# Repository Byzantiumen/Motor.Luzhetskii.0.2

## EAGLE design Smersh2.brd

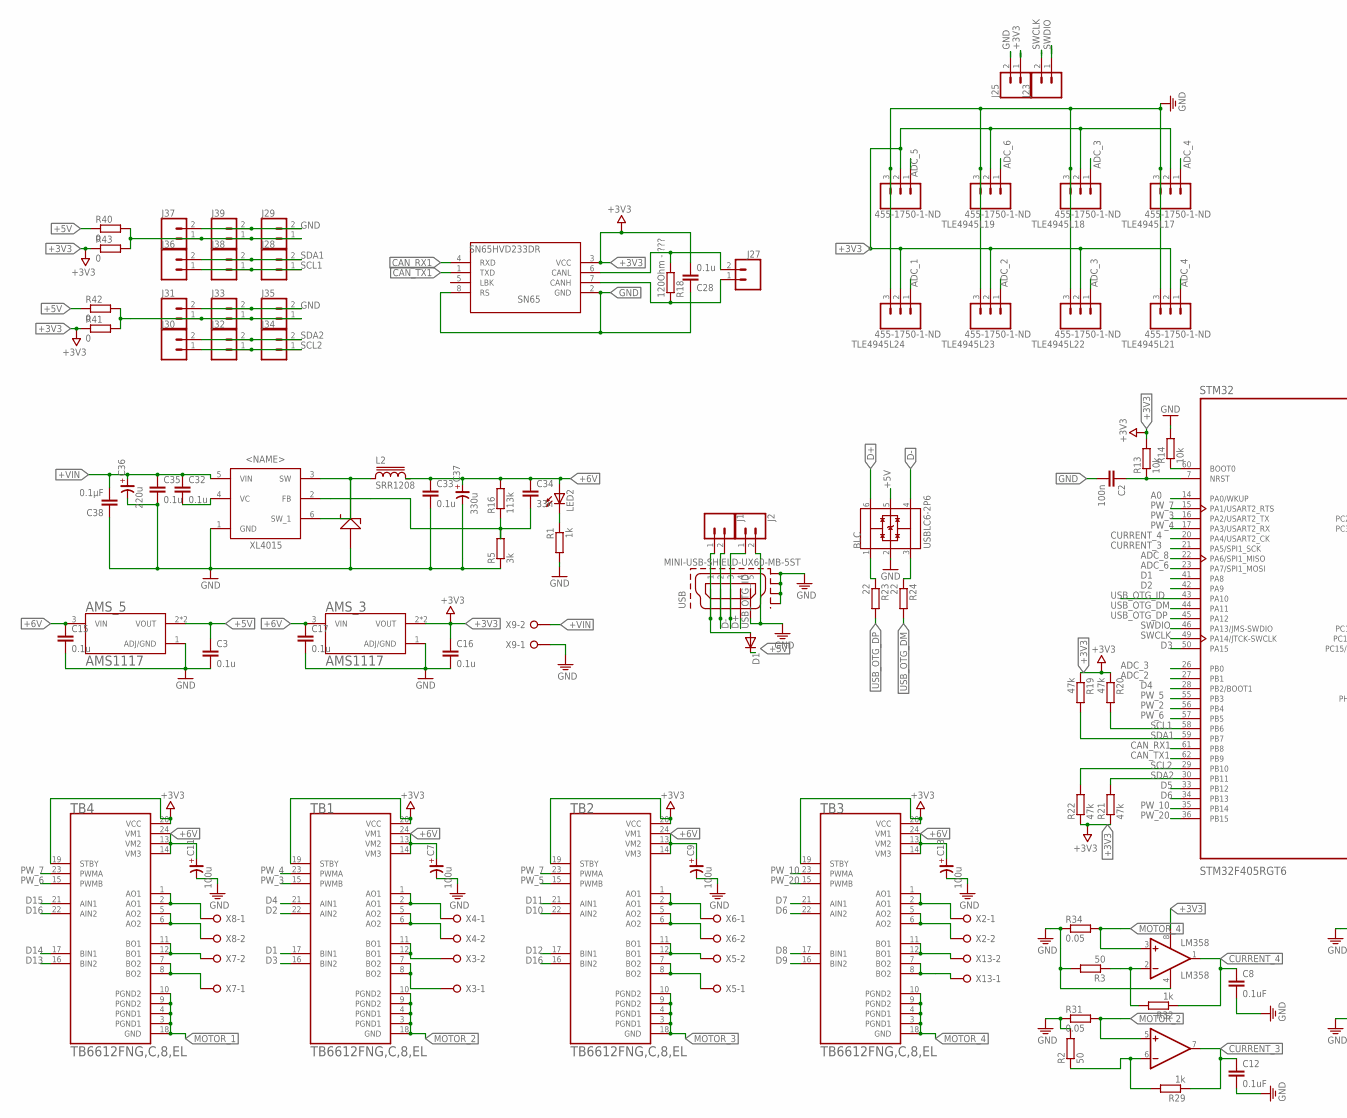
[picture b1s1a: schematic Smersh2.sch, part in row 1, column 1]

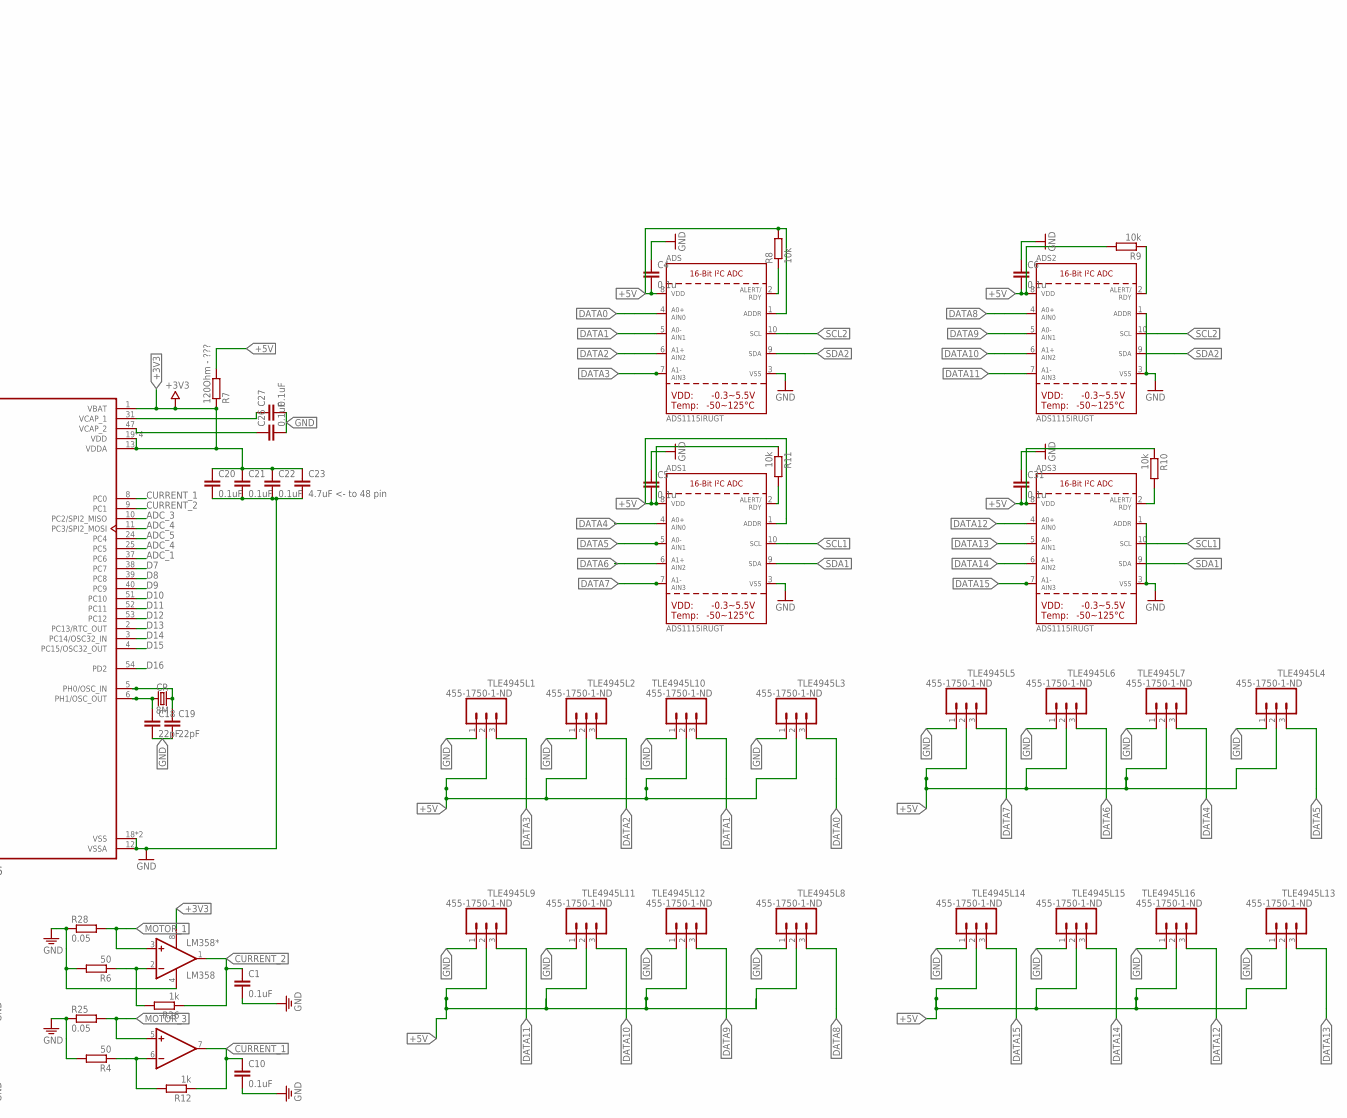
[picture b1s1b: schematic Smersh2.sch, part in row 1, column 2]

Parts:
ADS, ADS1, ADS2, ADS3: ADS1115IRUGT; MSOP10
AMS_3, AMS_5: AMS1117; SOT229P700X180-4N
BLC: USBLC6-2P6; SOT50P160X60-6N
C1, C8, C10, C12, C20, C21, C22, C26, C27: 0.1uF; C0603
C2: 100n; C0603
C3, C4, C5, C6, C15, C16, C17, C28, C31, C32, C33, C35: 0.1u; C0603
C7, C9, C11, C13: 100u; CSV-B
C18, C19: 22pF; C0603
C23: 4.7uF <- to 48 pin; C0603
C34: 33n; C0603
C36: 220u; CSV-D
C37: 330u; CSV-D
C38: 0.1µF; C0603
CR: 8M; CRYSTAL-SMD-3.2X2.5MM
D1: DIODE-MELF-MLL41; MELF-MLL41
DIOD: SK54; DO214AA
J1, J2, J23, J25, J27, J28, J29, J30, J31, J32, J33, J34, J35, J36, J37, J38, J39: CONN_02; 1X02
L2: SRR1208; SSR1208
LED2: LEDCHIPLED_0805; CHIPLED_0805
LM358, LM358*: LM358
R1, R12, R26, R29, R32: 1k; R0603
R2, R3, R4, R6: 50; R0603
R5: 3k; M0805
R7: 120Ohm - ???; R0805
R8, R9, R10, R11, R13, R14: 10k; R0603
R16: 113k; M0805
R18: 120Ohm - ???; R0603
R19, R20, R21, R22: 47k; R0603
R23, R24: 22; R0805
R25, R28, R31, R34: 0.05; R1206
R40, R41, R42, R43: 0; R0805
SN65: SN65HVD233DR; SOIC8
STM32: STM32F405RGT6; QFP50P1200X1200X160-64N
TB1, TB2, TB3, TB4: TB6612FNG,C,8,EL; SOP65P760X160-24N
TLE4945L1, TLE4945L2, TLE4945L3, TLE4945L4, TLE4945L5, TLE4945L6, TLE4945L7, TLE4945L8, TLE4945L9, TLE4945L10, TLE4945L11, TLE4945L12, TLE4945L13, TLE4945L14, TLE4945L15, TLE4945L16, TLE4945L17, TLE4945L18, TLE4945L19, TLE4945L20, TLE4945L21, TLE4945L22, TLE4945L23, TLE4945L24: 455-1750-1-ND; 1X03
USB: MINI-USB-SHIELD-UX60-MB-5ST; UX60-MB-5ST
X2, X3, X4, X5, X6, X7, X8, X9, X13: W237-02P; W237-132
XL4015: XL4015; TO263-5L

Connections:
+3V3: AMS_3.2 (VOUT), AMS_3.4 (VOUT), C16.1, C20.1, C21.1, C22.1, C23.1, C28.2, J25.1, LM358.8 (V+), LM358*.8 (V+), R7.1, R13.2, R19.1, R20.1, R21.1, R22.1, R41.1, R43.1, SN65.3 (VCC), STM32.1 (VBAT), STM32.13 (VDDA), STM32.19 (VDD), STM32.32 (VDD), STM32.48 (VDD), STM32.64 (VDD), TB1.19 (STBY), TB1.20 (VCC), TB2.19 (STBY), TB2.20 (VCC), TB3.19 (STBY), TB3.20 (VCC), TB4.19 (STBY), TB4.20 (VCC), TLE4945L17.2, TLE4945L18.2, TLE4945L19.2, TLE4945L20.2, TLE4945L21.2, TLE4945L22.2, TLE4945L23.2, TLE4945L24.2
+5V: ADS.1 (ADDR), ADS.8 (VDD), ADS1.1 (ADDR), ADS1.8 (VDD), ADS2.8 (VDD), ADS3.8 (VDD), AMS_5.2 (VOUT), AMS_5.4 (VOUT), BLC.5 (VBUS), C3.1, C4.2, C5.2, C6.2, C31.2, D1.C, R7.2, R8.2, R9.2, R10.1, R11.1, R40.1, R42.1, TLE4945L1.2, TLE4945L2.2, TLE4945L3.2, TLE4945L4.2, TLE4945L5.2, TLE4945L6.2, TLE4945L7.2, TLE4945L8.2, TLE4945L9.2, TLE4945L10.2, TLE4945L11.2, TLE4945L12.2, TLE4945L13.2, TLE4945L14.2, TLE4945L15.2, TLE4945L16.2
+6V: AMS_3.3 (VIN), AMS_5.3 (VIN), C7.+, C9.+, C11.+, C13.+, C15.1, C17.1, C33.1, C34.1, C37.+, L2.2, LED2.A, R16.2, TB1.13 (VM2), TB1.14 (VM3), TB1.24 (VM1), TB2.13 (VM2), TB2.14 (VM3), TB2.24 (VM1), TB3.13 (VM2), TB3.14 (VM3), TB3.24 (VM1), TB4.13 (VM2), TB4.14 (VM3), TB4.24 (VM1)
+VIN: C32.1, C35.1, C36.+, C38.2, X9.2, XL4015.5 (VIN)
A0: STM32.14 (PA0/WKUP)
ADC_1: STM32.37 (PC6), TLE4945L24.1
ADC_2: STM32.27 (PB1), TLE4945L23.1
ADC_3: STM32.10 (PC2/SPI2_MISO), STM32.26 (PB0), TLE4945L18.1, TLE4945L22.1
ADC_4: STM32.11 (PC3/SPI2_MOSI), STM32.25 (PC5), TLE4945L17.1, TLE4945L21.1
ADC_5: STM32.24 (PC4), TLE4945L20.1
ADC_6: STM32.23 (PA7/SPI1_MOSI), TLE4945L19.1
ADC_8: STM32.22 (PA6/SPI1_MISO)
CANH2: J27.1, R18.1, SN65.7 (CANH)
CANL2: J27.2, R18.2, SN65.6 (CANL)
CAN_RX1: SN65.4 (RXD), STM32.61 (PB8)
CAN_TX1: SN65.1 (TXD), STM32.62 (PB9)
CURRENT_1: C10.1, LM358*.7 (OUT1), R12.1, STM32.8 (PC0)
CURRENT_2: C1.1, LM358*.1 (OUT), R26.1, STM32.9 (PC1)
CURRENT_3: C12.1, LM358.7 (OUT1), R29.1, STM32.21 (PA5/SPI1_SCK)
CURRENT_4: C8.1, LM358.1 (OUT), R32.1, STM32.20 (PA4/USART2_CK)
D1: STM32.41 (PA8), TB1.17 (BIN1)
D2: STM32.42 (PA9), TB1.22 (AIN2)
D3: STM32.50 (PA15), TB1.16 (BIN2)
D4: STM32.28 (PB2/BOOT1), TB1.21 (AIN1)
D5: STM32.33 (PB12)
D6: STM32.34 (PB13), TB3.22 (AIN2)
D7: STM32.38 (PC7), TB3.21 (AIN1)
D8: STM32.39 (PC8), TB3.17 (BIN1)
D9: STM32.40 (PC9), TB3.16 (BIN2)
D10: STM32.51 (PC10), TB2.22 (AIN2)
D11: STM32.52 (PC11), TB2.21 (AIN1)
D12: STM32.53 (PC12), TB2.17 (BIN1)
D13: STM32.2 (PC13/RTC_OUT), TB4.16 (BIN2)
D14: STM32.3 (PC14/OSC32_IN), TB4.17 (BIN1)
D15: STM32.4 (PC15/OSC32_OUT), TB4.21 (AIN1)
D16: STM32.54 (PD2), TB2.16 (BIN2), TB4.22 (AIN2)
D+: BLC.6 (I/O1_2), J2.1, USB.3
D-: BLC.4 (I/O2_2), J1.2, USB.2
DATA0: ADS.4 (AIN0), TLE4945L3.3
DATA1: ADS.5 (AIN1), TLE4945L10.3
DATA2: ADS.6 (AIN2), TLE4945L2.3
DATA3: ADS.7 (AIN3), TLE4945L1.3
DATA4: ADS1.4 (AIN0), TLE4945L7.3
DATA5: ADS1.5 (AIN1), TLE4945L4.3
DATA6: ADS1.6 (AIN2), TLE4945L6.3
DATA7: ADS1.7 (AIN3), TLE4945L5.3
DATA8: ADS2.4 (AIN0), TLE4945L8.3
DATA9: ADS2.5 (AIN1), TLE4945L12.3
DATA10: ADS2.6 (AIN2), TLE4945L11.3
DATA11: ADS2.7 (AIN3), TLE4945L9.3
DATA12: ADS3.4 (AIN0), TLE4945L16.3
DATA13: ADS3.5 (AIN1), TLE4945L13.3
DATA14: ADS3.6 (AIN2), TLE4945L15.3
DATA15: ADS3.7 (AIN3), TLE4945L14.3
GND: ADS.3 (VSS), ADS1.3 (VSS), ADS2.1 (ADDR), ADS2.3 (VSS), ADS3.1 (ADDR), ADS3.3 (VSS), AMS_3.1 (ADJ/GND), AMS_5.1 (ADJ/GND), BLC.2 (GND), C1.2, C2.2, C3.2, C4.1, C5.1, C6.1, C7.-, C8.2, C9.-, C10.2, C11.-, C12.2, C13.-, C15.2, C16.2, C17.2, C18.2, C19.2, C20.2, C21.2, C22.2, C23.2, C26.2, C27.2, C28.1, C31.1, C33.2, C35.2, C36.-, C37.-, C38.1, DIOD.A (1), J2.2, J25.2, J29.2, J31.2, J33.2, J35.2, J37.2, J39.2, LM358.4 (V-), LM358*.4 (V-), R1.2, R2.2, R3.2, R4.2, R5.1, R6.2, R14.2, R25.1, R28.1, R31.1, R34.1, SN65.2 (GND), SN65.8 (RS), STM32.12 (VSSA), STM32.18 (VSS), STM32.63 (VSS), TLE4945L1.1, TLE4945L2.1, TLE4945L3.1, TLE4945L4.1, TLE4945L5.1, TLE4945L6.1, TLE4945L7.1, TLE4945L8.1, TLE4945L9.1, TLE4945L10.1, TLE4945L11.1, TLE4945L12.1, TLE4945L13.1, TLE4945L14.1, TLE4945L15.1, TLE4945L16.1, TLE4945L17.3, TLE4945L18.3, TLE4945L19.3, TLE4945L20.3, TLE4945L21.3, TLE4945L22.3, TLE4945L23.3, TLE4945L24.3, USB.5, USB.M1 (GND1), USB.M2 (GND2), USB.M3 (GND3), USB.M4 (GND4), X9.1, XL4015.1 (GND)
MOTOR_1: LM358*.3 (+IN), R28.2, TB4.3 (PGND1), TB4.4 (PGND1), TB4.9 (PGND2), TB4.10 (PGND2), TB4.18 (GND)
MOTOR_2: LM358.5 (+IN1), R31.2, TB1.3 (PGND1), TB1.4 (PGND1), TB1.9 (PGND2), TB1.10 (PGND2), TB1.18 (GND)
MOTOR_3: LM358*.5 (+IN1), R25.2, TB2.3 (PGND1), TB2.4 (PGND1), TB2.9 (PGND2), TB2.10 (PGND2), TB2.18 (GND)
MOTOR_4: LM358.3 (+IN), R34.2, TB3.3 (PGND1), TB3.4 (PGND1), TB3.9 (PGND2), TB3.10 (PGND2), TB3.18 (GND)
unnamed: ADS.2 (ALERT/RDY), R8.1
unnamed: LED2.C, R1.1
unnamed: D1.A, J1.1, USB.1
unnamed: ADS2.2 (ALERT/RDY), R9.1
unnamed: TB1.1 (AO1), TB1.2 (AO1), X4.1
unnamed: C32.2, XL4015.4 (VC)
unnamed: TB1.5 (AO2), TB1.6 (AO2), X4.2
unnamed: DIOD.C (2), L2.1, XL4015.3 (SW), XL4015.6 (SW_1)
unnamed: TB1.11 (BO1), TB1.12 (BO1), X3.2
unnamed: TB1.7 (BO2), TB1.8 (BO2), X3.1
unnamed: C2.1, R13.1, STM32.7 (NRST)
unnamed: C19.1, CR.3 (2), STM32.5 (PH0/OSC_IN)
unnamed: TB2.1 (AO1), TB2.2 (AO1), X6.1
unnamed: TB2.5 (AO2), TB2.6 (AO2), X6.2
unnamed: C18.1, CR.1, STM32.6 (PH1/OSC_OUT)
unnamed: ADS3.2 (ALERT/RDY), R10.2
unnamed: TB2.11 (BO1), TB2.12 (BO1), X5.2
unnamed: ADS1.2 (ALERT/RDY), R11.2
unnamed: R14.1, STM32.60 (BOOT0)
unnamed: C26.1, STM32.47 (VCAP_2)
unnamed: TB2.7 (BO2), TB2.8 (BO2), X5.1
unnamed: LM358*.6 (-IN1), R4.1, R12.2
unnamed: LM358*.2 (-IN), R6.1, R26.2
unnamed: C34.2, R5.2, R16.1, XL4015.2 (FB)
unnamed: TB4.1 (AO1), TB4.2 (AO1), X8.1
unnamed: TB4.5 (AO2), TB4.6 (AO2), X8.2
unnamed: TB4.11 (BO1), TB4.12 (BO1), X7.2
unnamed: TB4.7 (BO2), TB4.8 (BO2), X7.1
unnamed: LM358.6 (-IN1), R2.1, R29.2
unnamed: TB3.1 (AO1), TB3.2 (AO1), X2.1
unnamed: TB3.5 (AO2), TB3.6 (AO2), X2.2
unnamed: TB3.11 (BO1), TB3.12 (BO1), X13.2
unnamed: TB3.7 (BO2), TB3.8 (BO2), X13.1
unnamed: C27.1, STM32.31 (VCAP_1)
unnamed: LM358.2 (-IN), R3.1, R32.2
unnamed: BLC.1 (I/O1_1), R23.1
unnamed: BLC.3 (I/O2_1), R24.1
unnamed: J31.1, J33.1, J35.1, R41.2, R42.2
unnamed: J29.1, J37.1, J39.1, R40.2, R43.2
PW_2: STM32.56 (PB4)
PW_3: STM32.16 (PA2/USART2_TX), TB1.15 (PWMB)
PW_4: STM32.17 (PA3/USART2_RX), TB1.23 (PWMA)
PW_5: STM32.55 (PB3), TB2.15 (PWMB)
PW_6: STM32.57 (PB5), TB4.15 (PWMB)
PW_7: STM32.15 (PA1/USART2_RTS), TB2.23 (PWMA), TB4.23 (PWMA)
PW_10: STM32.35 (PB14), TB3.23 (PWMA)
PW_20: STM32.36 (PB15), TB3.15 (PWMB)
SCL1: ADS1.10 (SCL), ADS3.10 (SCL), J28.1, J36.1, J38.1, R20.2, STM32.58 (PB6)
SCL2: ADS.10 (SCL), ADS2.10 (SCL), J30.1, J32.1, J34.1, R22.2, STM32.29 (PB10)
SDA1: ADS1.9 (SDA), ADS3.9 (SDA), J28.2, J36.2, J38.2, R19.2, STM32.59 (PB7)
SDA2: ADS.9 (SDA), ADS2.9 (SDA), J30.2, J32.2, J34.2, R21.2, STM32.30 (PB11)
SWCLK: J23.2, STM32.49 (PA14/JTCK-SWCLK)
SWDIO: J23.1, STM32.46 (PA13/JMS-SWDIO)
USB_OTG_DM: R24.2, STM32.44 (PA11)
USB_OTG_DP: R23.2, STM32.45 (PA12)
USB_OTG_ID: STM32.43 (PA10), USB.4

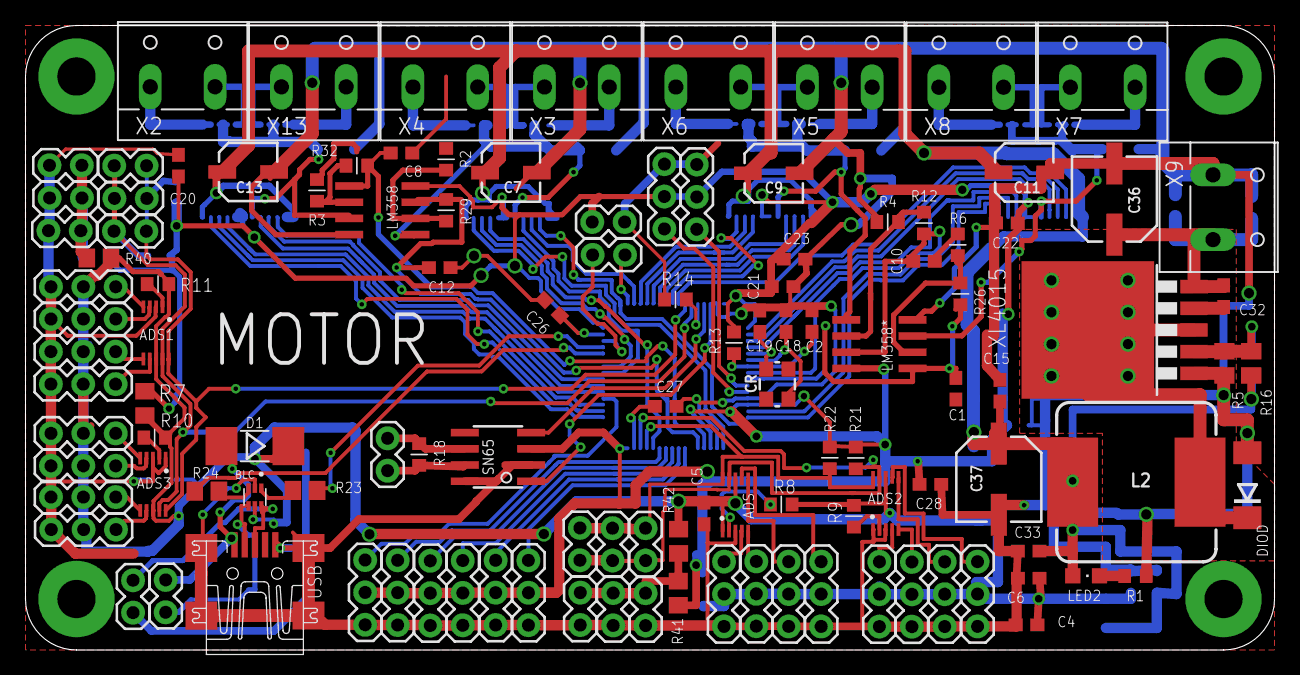
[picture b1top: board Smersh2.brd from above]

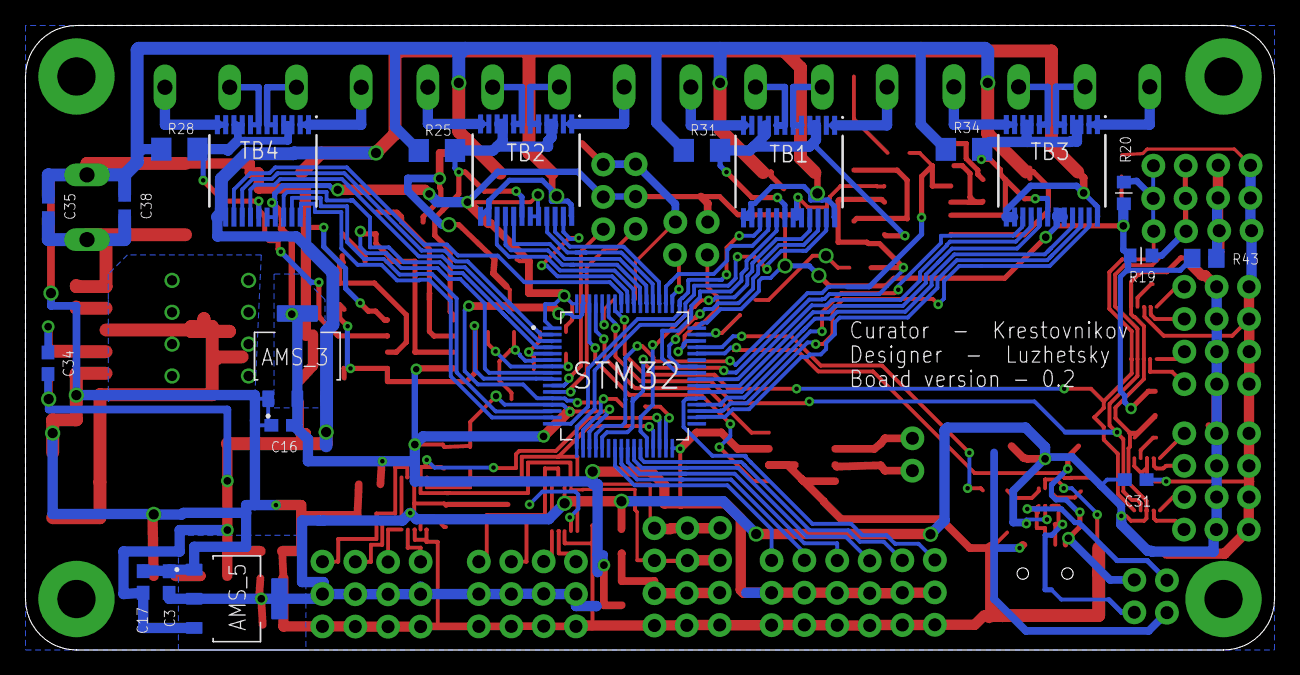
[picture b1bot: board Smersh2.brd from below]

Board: 2 copper layers, 98.0 x 49.0 mm, 138 parts (21 on the bottom side), 111 nets.

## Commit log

2020-07-23 Эти платы не требуют проверки
2020-07-26 Доработанные платы

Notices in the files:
parts and their libraries:
SparkFun-Connectors: Licensing: Creative Commons ShareAlike 4.0 International - https://creativecommons.org/licenses/by-sa/4.0
rc-master-smd: Copyright (C) 2007, Bob Starr
srr1208: Copyright (C) 2008, Bob Starr
